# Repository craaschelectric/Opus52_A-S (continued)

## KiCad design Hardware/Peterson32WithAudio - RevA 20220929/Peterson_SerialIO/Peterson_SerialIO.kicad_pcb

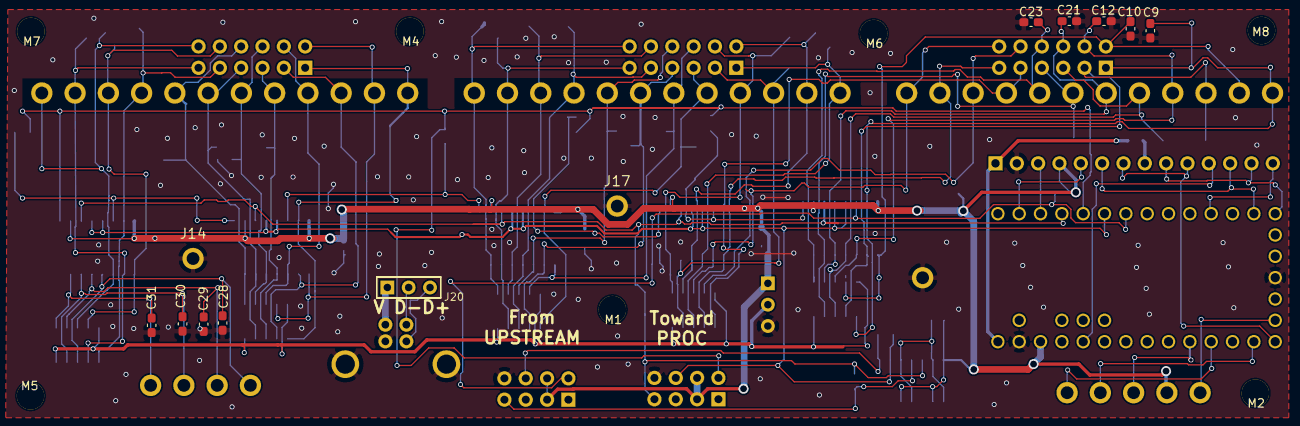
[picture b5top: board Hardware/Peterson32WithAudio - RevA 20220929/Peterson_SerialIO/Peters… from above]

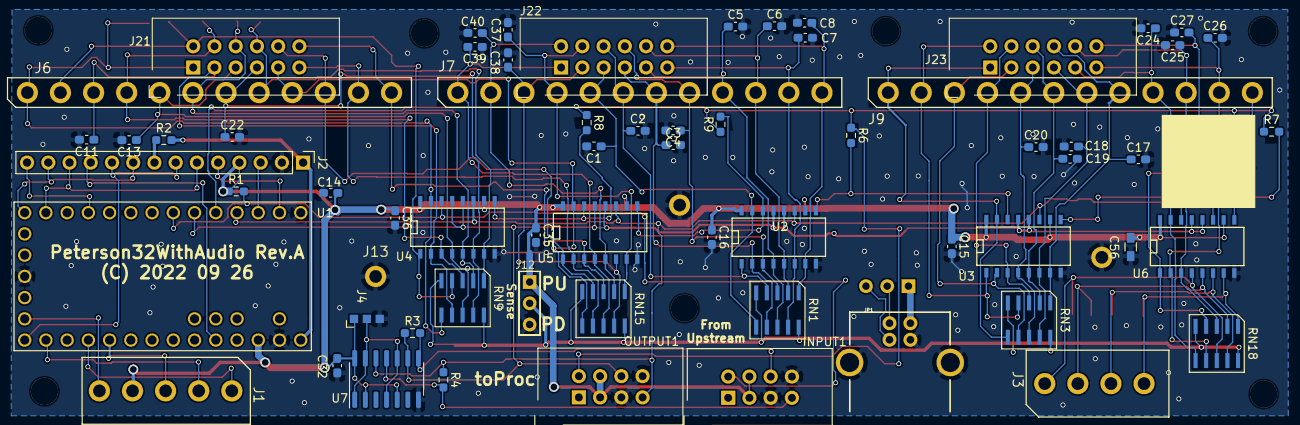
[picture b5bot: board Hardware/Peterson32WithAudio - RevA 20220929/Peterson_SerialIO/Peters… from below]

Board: 2 copper layers, 84 parts (64 on the bottom side), 70 nets.

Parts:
C1, C2, C3, C4, C5, C6, C7, C8, C9, C10, C11, C12, C13, C17, C18, C19, C20, C21, C22, C23, C37, C38, C39, C40: 1nF or ESD; C_0603_1608Metric_Pad1.08x0.95mm_HandSolder
C14, C15, C16, C32, C35, C36: C; C_0603_1608Metric_Pad1.08x0.95mm_HandSolder
C24, C25, C26, C27, C28, C29, C30, C31: ESD; C_0603_1608Metric_Pad1.08x0.95mm_HandSolder
C56: C; R_0603_HandSoldering
INPUT1: Conn_02x04_Counter_Clockwise; RibbonCableSocket_8_CCW
J1: Conn_01x05; KK156-5
J2: Conn_01x14; PinHeader_1x14_P2.54mm_Vertical
J3: Conn_01x04; KK156-4
J4: Conn_01x03; 0603Jumper
J6, J7, J9: Conn_01x12; KK156-12
J12: Conn_01x03; H3-2.54
J13, J14, J17: Conn_01x01; KK156-1
J20: Conn_01x03_Male; H3-2.54
J21, J22, J23: Conn_01x12; RibbonCableSocket_12_OddEven
JP1: DIP-USB-B-TYPE-FMAL_4+2P-2.0-90D_; USB4+2-2.5-90D-15.8X12MM
M1, M2, M4, M5, M6, M7, M8: Conn_01x01; Mounting#4
OUTPUT1: Conn_02x04_Counter_Clockwise; RibbonCableSocket_8_CCW
R1, R3, R4, R6, R7, R8, R9: DNP; R_0603_1608Metric_Pad0.98x0.95mm_HandSolder
R2: 100; R_0603_1608Metric_Pad0.98x0.95mm_HandSolder
RN1, RN3, RN9, RN15, RN18: R_Network08_10Pin; EXBA10P
U1: Teensy3.2; Teensy3.x_LC
U2, U3, U4, U5, U6: 74HC597; SO-16-N
U7: 74LS126; SOIC-14_3.9x8.7mm_P1.27mm

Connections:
+5V: J2.1, R2.2, U1.33
/ChainIn: INPUT1.8, R1.2, U1.7, U4.14
/D_C: J2.5, U1.2
/InRegLoad: OUTPUT1.6, R3.1, U1.6, U2.12, U2.13, U3.12, U3.13, U4.12, U4.13, U5.12, U5.13, U6.12, U6.13, U7.9
/MISO: J2.9, J2.13, U1.14
/MOSI: J2.6, J2.12, U1.13
/OUT0: C9.1, J6.1, J21.1, RN9.6, U4.15
/OUT1: C10.1, J6.2, J21.2, RN9.4, U4.1
/OUT2: C11.1, J6.3, J21.3, RN9.7, U4.2
/OUT3: C12.1, J6.4, J21.4, RN9.3, U4.3
/OUT4: C13.1, J6.5, J21.5, RN9.8, U4.4
/OUT5: C21.1, J6.6, J21.6, RN9.2, U4.5
/OUT6: C22.1, J6.7, J21.7, RN9.9, U4.6
/OUT7: C23.1, J6.8, J21.8, RN9.1, U4.7
/OUT8: J6.9, J21.9, RN15.6, U5.15
/OUT9: J6.10, J21.10, RN15.4, U5.1
/OUT10: J6.11, J21.11, RN15.7, U5.2
/OUT11: J6.12, J21.12, RN15.3, U5.3
/OUT12: C40.1, J7.1, J22.1, RN15.8, U5.4
/OUT13: C39.1, J7.2, J22.2, RN15.2, U5.5
/OUT14: C38.1, J7.3, J22.3, RN15.9, U5.6
/OUT15: C37.1, J7.4, J22.4, RN15.1, U5.7
/OUT16: C1.1, J7.5, J22.5, RN1.6, U2.15
/OUT17: C2.1, J7.6, J22.6, RN1.4, U2.1
/OUT18: C3.1, J7.7, J22.7, RN1.7, U2.2
/OUT19: C4.1, J7.8, J22.8, RN1.3, U2.3
/OUT20: C5.1, J7.9, J22.9, RN1.8, U2.4
/OUT21: C6.1, J7.10, J22.10, RN1.2, U2.5
/OUT22: C7.1, J7.11, J22.11, RN1.9, U2.6
/OUT23: C8.1, J7.12, J22.12, RN1.1, U2.7
/OUT24: J9.1, J23.1, RN3.6, U3.15
/OUT25: J9.2, J23.2, RN3.4, U3.1
/OUT26: J9.3, J23.3, RN3.7, U3.2
/OUT27: J9.4, J23.4, RN3.3, U3.3
/OUT28: C20.1, J9.5, J23.5, RN3.8, U3.4
/OUT29: C19.1, J9.6, J23.6, RN3.2, U3.5
/OUT30: C18.1, J9.7, J23.7, RN3.9, U3.6
/OUT31: C17.1, J9.8, J23.8, RN3.1, U3.7
/OUT32: C24.1, J9.9, J23.9, RN18.6, U6.15
/OUT33: C25.1, J9.10, J23.10, RN18.4, U6.1
/OUT34: C26.1, J9.11, J23.11, RN18.7, U6.2
/OUT35: C27.1, J9.12, J23.12, RN18.3, U6.3
/OUT36: C28.1, J3.1, RN18.8, U6.4
/OUT37: C29.1, J3.2, RN18.2, U6.5
/OUT38: C30.1, J3.3, RN18.9, U6.6
/OUT39: C31.1, J3.4, RN18.1, U6.7
/PULLTERM: J12.2, RN1.5, RN1.10, RN3.5, RN3.10, RN9.5, RN9.10, RN15.5, RN15.10, RN18.5, RN18.10
/Ports33_48/SERIn2: R7.2, U3.9, U6.14
/SCK: J2.7, J2.10, U1.20
/SEROut0: R9.2, U2.14, U5.9
/SerialCLK: OUTPUT1.4, R4.1, U1.4, U2.11, U3.11, U4.11, U5.11, U6.11, U7.12
/TFTCS: J2.3, U1.3
/T_CS: J2.11, U1.29
/T_IRQ: J2.14, U1.11
CHAINOUT: OUTPUT1.8, R6.1, R7.1, R8.1, R9.1, U1.5, U6.9
GND: C1.2, C2.2, C3.2, C4.2, C5.2, C6.2, C7.2, C8.2, C9.2, C10.2, C11.2, C12.2, C13.2, C14.2, C15.2, C16.2, C17.2, C18.2, C19.2, C20.2, C21.2, C22.2, C23.2, C24.2, C25.2, C26.2, C27.2, C28.2, C29.2, C30.2, C31.2, C32.2, C35.2, C36.2, C37.2, C38.2, C39.2, C40.2, C56.2, INPUT1.3, INPUT1.5, J2.2, J4.3, J12.3, J13.1, J14.1, J17.1, JP1.GND, JP1.S1, JP1.S2, OUTPUT1.3, OUTPUT1.5, U1.1, U1.17, U1.32, U2.8, U3.8, U4.8, U5.8, U6.8, U7.7
unnamed: INPUT1.4, R4.2, U7.11
unnamed: INPUT1.6, R3.2, U7.8
unnamed: J1.1, U1.23
unnamed: J1.2, U1.21
unnamed: J1.3, U1.24
unnamed: J1.5, U1.19
unnamed: J2.8, R2.1
unnamed: J4.2, U7.1, U7.4, U7.10, U7.13
unnamed: J20.1, JP1.VBUS
unnamed: J20.2, JP1.D-
unnamed: J20.3, JP1.D+
unnamed: R6.2, U2.9, U3.14
unnamed: R8.2, U4.9, U5.14
VCC: C14.1, C15.1, C16.1, C32.1, C35.1, C36.1, C56.1, INPUT1.2, INPUT1.7, J1.4, J2.4, J4.1, J12.1, OUTPUT1.2, OUTPUT1.7, R1.1, U1.31, U2.10, U2.16, U3.10, U3.16, U4.10, U4.16, U5.10, U5.16, U6.10, U6.16, U7.2, U7.5, U7.14

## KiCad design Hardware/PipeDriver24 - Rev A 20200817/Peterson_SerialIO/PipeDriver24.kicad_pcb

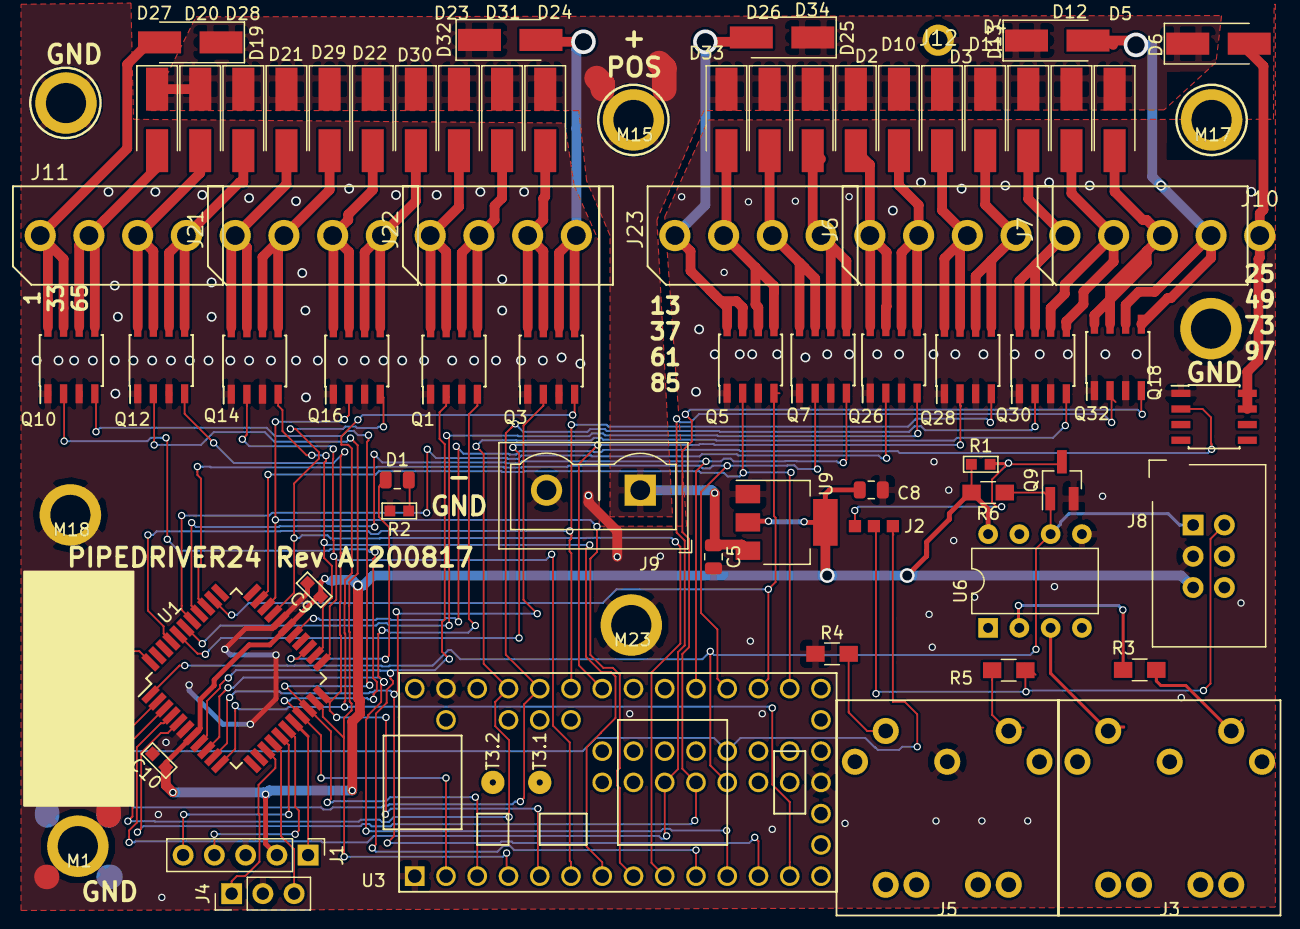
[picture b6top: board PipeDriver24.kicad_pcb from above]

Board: 2 copper layers, 76 parts (0 on the bottom side), 69 nets.

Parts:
C5, C8: CERAMIC-100NF-50V-10%-X7R_0603_; C_0805_2012Metric
C9: 1u; R0603
C10: 0.1u; R0603
D1: SMD-LED-CLEAR-GREEN_0805_; R_0805_2012Metric
D2, D3, D4, D5, D6, D10, D11, D12, D13, D19, D20, D21, D22, D23, D24, D25, D26, D27, D28, D29, D30, D31, D32, D33, D34: SK34; D_SMA_Handsoldering
J1: Conn_01x05; PinHeader_1x05_P2.54mm_Vertical
J2: Conn_01x03_Male; 0603Jumper
J3, J5: DIN-5; DIN5_KCDX-5S-S2
J4: Conn_01x03_Male; PinHeader_1x03_P2.54mm_Vertical
J6, J7, J11, J21, J22, J23: Conn_01x04_Male; KK156-4
J8: Conn_02x03_Odd_Even; RibbonCableSocket_6_OddEven
J9: Conn_01x02_Female; TerminalBlock_Wuerth_691311400102_P7.62mm
J10: Conn_01x01_Male; KK156-1
J12: Conn_01x01; KK156-1
M1, M15, M17, M18, M21, M23, M26: Conn_01x01; Mounting#4
Q1, Q3, Q5, Q7, Q10, Q12, Q14, Q16, Q18, Q26, Q28, Q30, Q32: SI4288; SOIC-8_3.9x4.9mm_P1.27mm
Q9: AO3404; SOT-23_Handsoldering
R1: 220; R0603
R2: DNP; R0603
R3, R4, R5, R6: 220; R_0805_HandSoldering
U1: PIC16F15375-IPT; LQFP-44_10x10mm_P0.8mm
U3: Teensy3.0; Teensy30_31_32_LC
U6: 6N138; DIP-8_W7.62mm
U9: AP1117-33; SOT-223-3_TabPin2

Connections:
/DRVA00: Q10.2, U1.19, U3.2
/DRVA01: Q10.4, U1.20, U3.3
/DRVA02: Q12.2, U1.21, U3.4
/DRVA03: Q12.4, U1.22, U3.5
/DRVA04: Q14.2, U1.23, U3.6
/DRVA05: Q14.4, U1.24, U3.7
/DRVA06: Q16.2, U1.31, U3.8
/DRVA07: Q16.4, U1.30, U3.9
/DRVA08: Q1.2, U1.8, U3.10
/DRVA09: Q1.4, U1.9, U3.11
/DRVA10: Q3.2, U1.10, U3.12
/DRVA11: Q3.4, U1.11, U3.13
/DRVA12: Q5.2, U1.32, U3.21
/DRVA13: Q5.4, U1.35, U3.22
/DRVA14: Q7.2, U1.36, U3.23
/DRVA15: Q7.4, U1.37, U3.24
/DRVB00: Q26.2, U1.38
/DRVB01: Q26.4, U1.39
/DRVB02: Q28.2, U1.40, U3.27
/DRVB03: Q28.4, U1.41, U3.28
/DRVB04: Q30.2, U1.2, U3.29
/DRVB05: Q30.4, U1.3, U3.30
/DRVB06: Q32.2, U1.4, U3.40
/DRVB07: Q32.4, U1.5, U3.41
/DRVB08: Q18.2, U1.27
/ICLK: J1.5, U1.16
/IDTA: J1.4, U1.17
/LEDDRV: D1.1, U1.25
/SAMA00: D19.1, J11.1, Q10.7, Q10.8
/SAMA01: D27.1, J11.2, Q10.5, Q10.6
/SAMA02: D20.1, J11.3, Q12.7, Q12.8
/SAMA03: D28.1, J11.4, Q12.5, Q12.6
/SAMA04: D21.1, J21.1, Q14.7, Q14.8
/SAMA05: D29.1, J21.2, Q14.5, Q14.6
/SAMA06: D22.1, J21.3, Q16.7, Q16.8
/SAMA07: D30.1, J21.4, Q16.5, Q16.6
/SAMA08: D23.1, J22.1, Q1.7, Q1.8
/SAMA09: D31.1, J22.2, Q1.5, Q1.6
/SAMA10: D24.1, J22.3, Q3.7, Q3.8
/SAMA11: D32.1, J22.4, Q3.5, Q3.6
/SAMA12: D25.1, J23.1, Q5.7, Q5.8
/SAMA13: D33.1, J23.2, Q5.5, Q5.6
/SAMA14: D26.1, J23.3, Q7.7, Q7.8
/SAMA15: D34.1, J23.4, Q7.5, Q7.6
/SAMB00: D2.1, J6.1, Q26.7, Q26.8
/SAMB01: D10.1, J6.2, Q26.5, Q26.6
/SAMB02: D3.1, J6.3, Q28.7, Q28.8
/SAMB03: D11.1, J6.4, Q28.5, Q28.6
/SAMB04: D4.1, J7.1, Q30.7, Q30.8
/SAMB05: D12.1, J7.2, Q30.5, Q30.6
/SAMB06: D5.1, J7.3, Q32.7, Q32.8
/SAMB07: D13.1, J7.4, Q32.5, Q32.6
/SAMB08: D6.1, J10.1, Q18.7, Q18.8
/SERDRV: J2.2, J8.2, R5.2
/SERIN: J8.1, Q9.1, R6.1, U1.1, U3.42, U6.6
/nMCLR: J1.1, U1.18
GND: C5.2, C8.2, C9.2, C10.2, J1.3, J4.2, J5.3, J8.3, J9.2, M1.1, M18.1, M21.1, M23.1, M26.1, Q1.1, Q1.3, Q3.1, Q3.3, Q5.1, Q5.3, Q7.1, Q7.3, Q9.2, Q10.1, Q10.3, Q12.1, Q12.3, Q14.1, Q14.3, Q16.1, Q16.3, Q18.1, Q26.1, Q26.3, Q28.1, Q28.3, Q30.1, Q30.3, Q32.1, Q32.3, R2.2, R4.1, U1.6, U1.29, U3.1, U3.17, U3.32, U6.5, U9.1
unnamed: D1.2, R2.1
unnamed: J2.1, U1.44, U3.47
unnamed: J2.3, Q9.3, R1.2
unnamed: J3.2, R3.2
unnamed: J3.4, U6.3
unnamed: J4.1, U1.14
unnamed: J4.3, U1.15
unnamed: J5.2, R5.1
unnamed: J5.4, R4.2
unnamed: R3.1, U6.2
SAMPWR: C5.1, D2.2, D3.2, D4.2, D5.2, D6.2, D10.2, D11.2, D12.2, D13.2, D19.2, D20.2, D21.2, D22.2, D23.2, D24.2, D25.2, D26.2, D27.2, D28.2, D29.2, D30.2, D31.2, D32.2, D33.2, D34.2, J9.1, J12.1, M15.1, U9.3
VCC: C8.1, C9.1, C10.1, J1.2, J8.5, R1.1, R6.2, U1.7, U1.28, U6.8, U9.2
